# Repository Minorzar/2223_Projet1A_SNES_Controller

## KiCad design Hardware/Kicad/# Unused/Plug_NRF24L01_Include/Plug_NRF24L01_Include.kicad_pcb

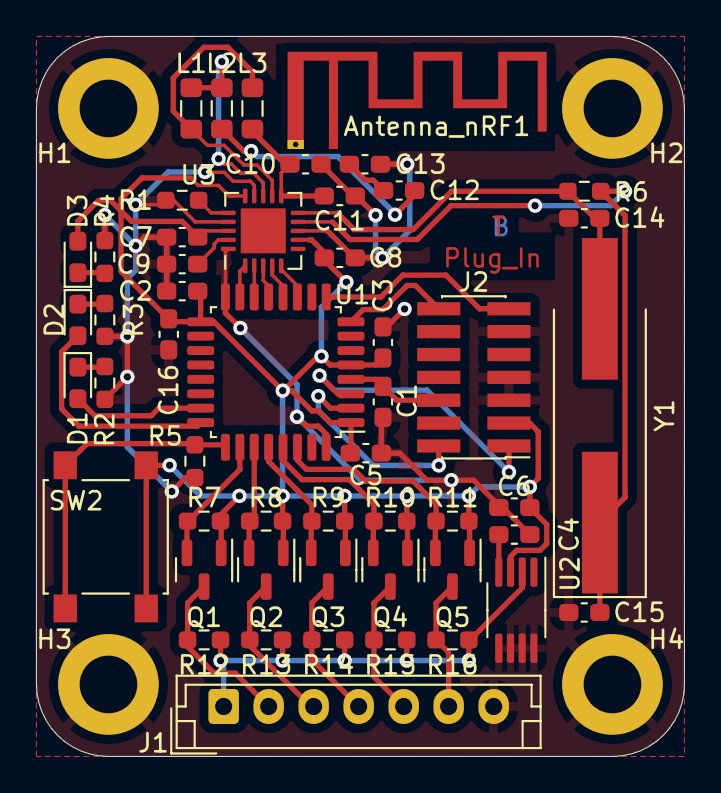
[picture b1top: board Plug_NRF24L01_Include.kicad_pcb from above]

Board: 2 copper layers, 36.0 x 40.0 mm, 55 parts (0 on the bottom side), 39 nets.

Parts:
Antenna_nRF1: Texas_SWRA117D_2.4GHz_Right
C1, C2, C3, C5: 100n; C_0603_1608Metric_Pad1.08x0.95mm_HandSolder
C4: 470p; C_0603_1608Metric_Pad1.08x0.95mm_HandSolder
C6: 2.2u; C_0603_1608Metric_Pad1.08x0.95mm_HandSolder
C7: 10n; C_0603_1608Metric_Pad1.08x0.95mm_HandSolder
C8: 1n; C_0603_1608Metric_Pad1.08x0.95mm_HandSolder
C9: 33n; C_0603_1608Metric_Pad1.08x0.95mm_HandSolder
C10: 2.2n; C_0603_1608Metric_Pad1.08x0.95mm_HandSolder
C11: 4.7p; C_0603_1608Metric_Pad1.08x0.95mm_HandSolder
C12: 1.5p; C_0603_1608Metric_Pad1.08x0.95mm_HandSolder
C13: 1.0p; C_0603_1608Metric_Pad1.08x0.95mm_HandSolder
C14, C15: 22p; C_0603_1608Metric_Pad1.08x0.95mm_HandSolder
C16: 10u; C_0603_1608Metric_Pad1.08x0.95mm_HandSolder
D1, D2: LED_Small; D_0603_1608Metric_Pad1.05x0.95mm_HandSolder
D3: LED; D_0603_1608Metric_Pad1.05x0.95mm_HandSolder
H1, H2, H3, H4: MountingHole_Pad; MountingHole_3.2mm_M3_DIN965_Pad
J1: Conn_01x07_Socket; JST_EH_B7B-EH-A_1x07_P2.50mm_Vertical
J2: Conn_02x07_Odd_Even; PinHeader_2x07_P1.27mm_Vertical_SMD
L1: 8.2n; L_0805_2012Metric_Pad1.05x1.20mm_HandSolder
L2: 3.9n; L_0805_2012Metric_Pad1.05x1.20mm_HandSolder
L3: 2.7n; L_0805_2012Metric_Pad1.05x1.20mm_HandSolder
Q1, Q2, Q3, Q4, Q5: 2N7002; SOT-23
R1: 22k; R_0603_1608Metric_Pad0.98x0.95mm_HandSolder
R2, R3, R4: 1k; R_0603_1608Metric_Pad0.98x0.95mm_HandSolder
R5, R7, R8, R9, R10, R11, R12, R13, R14, R15, R16: 10k; R_0603_1608Metric_Pad0.98x0.95mm_HandSolder
R6: 1M; R_0603_1608Metric_Pad0.98x0.95mm_HandSolder
SW2: SW_SPST; SW_SPST_B3S-1000
U1: STM32L412KBTx; LQFP-32_7x7mm_P0.8mm
U2: MIC5219-3.3YMM; MSOP-8_3x3mm_P0.65mm
U3: nRF24L01P; QFN-20-1EP_4x4mm_P0.5mm_EP2.5x2.5mm
Y1: 16MHz; Crystal_SMD_HC49-SD_HandSoldering

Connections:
+3.3V: C2.1, C3.1, C5.1, C6.1, C7.1, C8.1, C16.1, D3.2 (A), J2.3, Q1.1 (G), Q2.1 (G), Q3.1 (G), Q4.1 (G), Q5.1 (G), R7.1, R8.1, R9.1, R10.1, R11.1, SW2.2 (B), U1.1 (VDD), U1.5 (VDDA), U1.17 (VDD), U2.3 (OUT), U3.7 (VDD), U3.15 (VDD), U3.18 (VDD)
+5V: J1.1, R12.1, R13.1, R14.1, R15.1, R16.1, U2.2 (IN)
ANT1: L1.2, L3.1, U3.12 (ANT1)
ANT2: L1.1, L2.1, U3.13 (ANT2)
Appairing_Btn: R5.1, SW2.1 (A), U1.25 (PA15)
Chip_Enable: U1.15 (PB1), U3.1 (CE)
Data_Clock_SNES: J1.2, Q1.3 (D), R12.2
Data_Clock_STM32: Q1.2 (S), R7.2, U1.26 (PB3)
Data_Latch_SNES: J1.3, Q2.3 (D), R13.2
Data_Latch_STM32: Q2.2 (S), R8.2, U1.27 (PB4)
GND: C1.1, C2.2, C3.2, C4.2, C5.2, C6.2, C7.2, C8.2, C9.2, C10.2, C11.2, C13.1, C14.2, C15.2, C16.2, H1.1, H2.1, H3.1, H4.1, J1.7, J2.5, J2.7, J2.11, R1.2, R2.2, R3.2, R4.2, R5.2, U1.16 (VSS), U1.32 (VSS), U2.5 (GND), U2.6 (GND), U2.7 (GND), U2.8 (GND), U3.8 (VSS), U3.14 (VSS), U3.17 (VSS), U3.20 (VSS)
IOBit_SNES: J1.6, Q5.3 (D), R16.2
IOBit_STM32: Q5.2 (S), R11.2, U1.30 (PB7)
NRST: C1.2, J2.6, U1.4 (NRST)
unnamed: C12.2, L2.2
unnamed: D1.1 (K), R2.1
unnamed: D2.1 (K), R3.1
unnamed: D3.1 (K), R4.1
unnamed: C4.1, U2.4 (BP)
unnamed: C9.1, U3.19 (DVDD)
unnamed: R1.1, U3.16 (IREF)
Player1_LED: D1.2 (A), U1.23 (PA13)
RF_Output: Antenna_nRF1.1 (Feed_point), C12.1, C13.2
SPI_Chip_Select: U1.14 (PB0), U3.2 (CSN)
SPI_Clock: U1.13 (PA7), U3.3 (SCK)
SPI_Digital_Input: U1.12 (PA6), U3.4 (MOSI)
SPI_Digital_Output: U1.11 (PA5), U3.5 (MISO)
SWDCK: J2.14, U1.8 (PA2)
SWDIO: J2.13, U1.9 (PA3)
Serial_Data1_SNES: J1.4, Q3.3 (D), R14.2
Serial_Data1_STM32: Q3.2 (S), R9.2, U1.28 (PB5)
Serial_Data2_SNES: J1.5, Q4.3 (D), R15.2
Serial_Data2_STM32: Q4.2 (S), R10.2, U1.29 (PB6)
Status_LED: D2.2 (A), U1.24 (PA14)
USART2_RX: J2.1, U1.3 (PC15)
USART2_TX: J2.2, U1.2 (PC14)
VDD_PA: C10.1, C11.1, L3.2, U3.11 (VDD_PA)
XC1: C14.1, R6.1, U3.10 (XC1), Y1.2
XC2: C15.1, R6.2, U3.9 (XC2), Y1.1

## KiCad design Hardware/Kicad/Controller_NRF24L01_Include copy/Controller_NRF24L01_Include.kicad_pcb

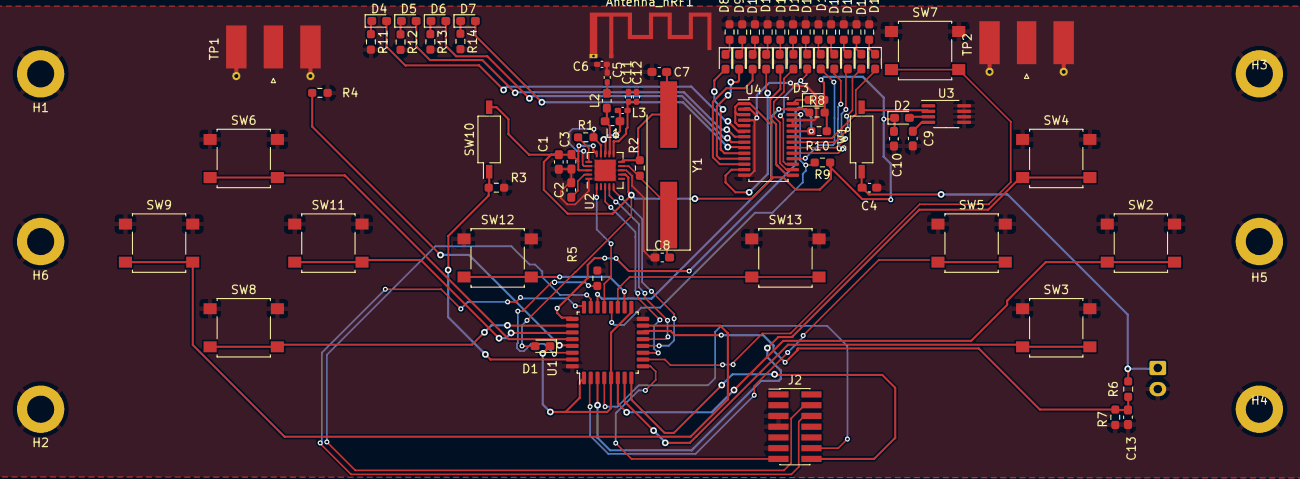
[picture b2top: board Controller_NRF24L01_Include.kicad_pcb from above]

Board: 2 copper layers, 90 parts (1 on the bottom side), 76 nets.

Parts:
Antenna_nRF1: Texas_SWRA117D_2.4GHz_Right
C1: 10nF; C_0603_1608Metric_Pad1.08x0.95mm_HandSolder
C2: 33nF; C_0603_1608Metric_Pad1.08x0.95mm_HandSolder
C3, C13: 1nF; C_0603_1608Metric_Pad1.08x0.95mm_HandSolder
C4: 1u; C_0603_1608Metric_Pad1.08x0.95mm_HandSolder
C5: 1.5pF; C_0402_1005Metric_Pad0.74x0.62mm_HandSolder
C6: 1.0pF; C_0402_1005Metric_Pad0.74x0.62mm_HandSolder
C7, C8: 22nF; C_0603_1608Metric_Pad1.08x0.95mm_HandSolder
C9: C_Small; C_0603_1608Metric_Pad1.08x0.95mm_HandSolder
C10: 100nF; C_0603_1608Metric_Pad1.08x0.95mm_HandSolder
C11: 2.2nF; C_0402_1005Metric_Pad0.74x0.62mm_HandSolder
C12: 4.7pF; C_0402_1005Metric_Pad0.74x0.62mm_HandSolder
D1: D_Small; D_0603_1608Metric_Pad1.05x0.95mm_HandSolder
D2: LED_Small; LED_0603_1608Metric_Pad1.05x0.95mm_HandSolder
D3: D_Small; LED_0603_1608Metric_Pad1.05x0.95mm_HandSolder
D4: G1; LED_0603_1608Metric_Pad1.05x0.95mm_HandSolder
D5: G2; LED_0603_1608Metric_Pad1.05x0.95mm_HandSolder
D6: G3; LED_0603_1608Metric_Pad1.05x0.95mm_HandSolder
D7: G4; LED_0603_1608Metric_Pad1.05x0.95mm_HandSolder
D8: G5; LED_0603_1608Metric_Pad1.05x0.95mm_HandSolder
D9: G6; LED_0603_1608Metric_Pad1.05x0.95mm_HandSolder
D10: G7; LED_0603_1608Metric_Pad1.05x0.95mm_HandSolder
D11: G8; LED_0603_1608Metric_Pad1.05x0.95mm_HandSolder
D12: O1; LED_0603_1608Metric_Pad1.05x0.95mm_HandSolder
D13: O2; LED_0603_1608Metric_Pad1.05x0.95mm_HandSolder
D14: O3; LED_0603_1608Metric_Pad1.05x0.95mm_HandSolder
D15: O4; LED_0603_1608Metric_Pad1.05x0.95mm_HandSolder
D16: R1; LED_0603_1608Metric_Pad1.05x0.95mm_HandSolder
D17: R2; LED_0603_1608Metric_Pad1.05x0.95mm_HandSolder
D18: R3; LED_0603_1608Metric_Pad1.05x0.95mm_HandSolder
D19: R4; LED_0603_1608Metric_Pad1.05x0.95mm_HandSolder
H1, H2, H3, H4, H5, H6: MountingHole_Pad; MountingHole_3.2mm_M3_DIN965_Pad
J1: Conn_01x02; JST_XH_B2B-XH-A_1x02_P2.50mm_Vertical
J2: Conn_02x07_Odd_Even; PinHeader_2x07_P1.27mm_Vertical_SMD
L1: 8.2nH; L_0603_1608Metric_Pad1.05x0.95mm_HandSolder
L2: 3.9nH; L_0603_1608Metric_Pad1.05x0.95mm_HandSolder
L3: 2.7nH; L_0402_1005Metric_Pad0.77x0.64mm_HandSolder
R1: 22K; R_0603_1608Metric_Pad0.98x0.95mm_HandSolder
R2, R6, R7: 1M; R_0603_1608Metric_Pad0.98x0.95mm_HandSolder
R3, R4, R5, R11, R12, R13, R14, R15, R16, R17, R18, R19, R20, R21, R22, R23, R24, R25, R26: 1K; R_0603_1608Metric_Pad0.98x0.95mm_HandSolder
R8, R9, R10: 10K; R_0603_1608Metric_Pad0.98x0.95mm_HandSolder
SW1, SW10: SW_DIP_x01; SW_DIP_SPSTx01_Slide_Copal_CHS-01B_W7.62mm_P1.27mm
SW2, SW3, SW4, SW5, SW6, SW7, SW8, SW9, SW11, SW12, SW13: SW_SPST; SW_SPST_B3S-1000
TP1: R; SMA_Molex_73251-1153_EdgeMount_Horizontal
TP2: L; SMA_Molex_73251-1153_EdgeMount_Horizontal
U1: STM32L412KBTx; LQFP-32_7x7mm_P0.8mm
U2: NRF24L01; QFN-20-1EP_4x4mm_P0.5mm_EP2.5x2.5mm
U3: MIC5219-3.3YMM; MSOP-8_3x3mm_P0.65mm
U4: PCA9685PW; TSSOP-28_4.4x9.7mm_P0.65mm
Y1: 16MHz; Crystal_SMD_HC49-SD_HandSoldering

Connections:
A_Button: SW2.2 (B), U1.6 (PA0)
Antenna: Antenna_nRF1.1 (Feed_point), C5.1, C6.1
B_Button: SW3.2 (B), U1.7 (PA1)
DC_Button: SW11.2 (B), U1.27 (PB4)
DIODE_CLK: R9.2, U1.20 (PA10), U4.26 (SCL)
DIODE_OE: R10.1, U1.25 (PA15), U4.23 (~OE)
DIODE_SDA: R8.1, U1.22 (PA12), U4.27 (SDA)
Digital_Out_Put: U1.12 (PA6), U2.5 (MISO)
GND: Antenna_nRF1.2 (GND), C1.2, C2.2, C3.2, C4.2, C6.2, C7.1, C8.1, C9.2, C10.2, C11.2, C12.1, C13.2, H1.1, H2.1, H3.1, H4.1, H5.1, H6.1, J1.2, J2.5, J2.7, J2.11, R1.2, R3.2, R4.2, R5.2, R7.2, R11.2, R12.2, R13.2, R14.2, R15.2, R16.2, R17.2, R18.2, R19.2, R20.2, R21.2, R22.2, R23.2, R24.2, R25.2, R26.2, SW2.1 (A), SW3.1 (A), SW4.1 (A), SW5.1 (A), SW6.1 (A), SW7.1 (A), SW8.1 (A), SW9.1 (A), SW11.1 (A), SW12.1 (A), SW13.1 (A), U1.16 (VSS), U1.32 (VSS), U2.8 (VSS), U2.14 (VSS), U2.17 (VSS), U2.20 (VSS), U3.5 (GND), U3.6 (GND), U3.7 (GND), U3.8 (GND), U4.2 (A1), U4.4 (A3), U4.14 (VSS), U4.24 (A5), U4.25 (EXTCLK)
Glob_Alim: C1.1, C3.1, C10.1, D1.2 (A), D2.1 (K), D3.2 (A), R8.2, R9.1, R10.2, SW10.2, U2.7 (VDD), U2.15 (VDD), U2.18 (VDD), U4.1 (A0), U4.3 (A2), U4.5 (A4)
L: R5.1, U1.30 (PB7)
LC_Button: SW8.2 (B), U1.26 (PB3)
Li-ion: C4.1, J1.1, R6.1, SW1.1
MOSI: U1.13 (PA7), U2.4 (MOSI)
NES/SNES_switcher: R3.1, SW10.1, U1.31 (PH3)
unnamed: D1.1 (K), U1.1 (VDD), U1.5 (VDDA), U1.17 (VDD)
unnamed: SW1.2, U3.2 (IN)
unnamed: D3.1 (K), U4.28 (VDD)
unnamed: C5.2, L2.2
unnamed: D2.2 (A), U3.3 (OUT)
unnamed: D4.2 (A), U4.6 (LED0)
unnamed: D4.1 (K), R11.1
unnamed: D5.2 (A), U4.7 (LED1)
unnamed: D5.1 (K), R12.1
unnamed: D6.2 (A), U4.8 (LED2)
unnamed: D6.1 (K), R13.1
unnamed: D7.2 (A), U4.9 (LED3)
unnamed: D7.1 (K), R14.1
unnamed: D8.2 (A), U4.10 (LED4)
unnamed: D8.1 (K), R15.1
unnamed: D9.2 (A), U4.11 (LED5)
unnamed: D9.1 (K), R16.1
unnamed: D10.2 (A), U4.12 (LED6)
unnamed: D10.1 (K), R17.1
unnamed: D11.2 (A), U4.13 (LED7)
unnamed: D11.1 (K), R18.1
unnamed: D12.2 (A), U4.15 (LED8)
unnamed: D12.1 (K), R19.1
unnamed: D13.2 (A), U4.16 (LED9)
unnamed: D13.1 (K), R20.1
unnamed: D14.2 (A), U4.17 (LED10)
unnamed: D14.1 (K), R21.1
unnamed: D15.2 (A), U4.18 (LED11)
unnamed: D15.1 (K), R22.1
unnamed: D16.2 (A), U4.19 (LED12)
unnamed: D16.1 (K), R23.1
unnamed: D17.2 (A), U4.20 (LED13)
unnamed: D17.1 (K), R24.1
unnamed: D18.2 (A), U4.21 (LED14)
unnamed: D18.1 (K), R25.1
unnamed: D19.2 (A), U4.22 (LED15)
unnamed: D19.1 (K), R26.1
unnamed: L1.2, L2.1, U2.12 (ANT1)
unnamed: L1.1, L3.1, U2.13 (ANT2)
unnamed: C2.1, U2.19 (DVDD)
unnamed: R1.1, U2.16 (IREF)
unnamed: C7.2, R2.1, U2.10 (XC1), Y1.2
unnamed: C8.2, R2.2, U2.9 (XC2), Y1.1
unnamed: C9.1, U3.4 (BP)
Order_Search: SW7.2 (B), U1.10 (PA4)
POWER_CHECK: C13.1, R6.2, R7.1, U1.14 (PB0)
Pin_Clock: U1.11 (PA5), U2.3 (SCK)
R: R4.1, U1.29 (PB6)
RC_Button: SW9.2 (B), U1.15 (PB1)
RX/TX: U1.21 (PA11), U2.1 (CE)
Reset_Buton: J2.12, U1.4 (NRST)
Return_ANT: C11.1, C12.2, L3.2, U2.11 (VDD_PA)
SE_Button: SW13.2 (B), U1.19 (PA9)
ST_Button: SW12.2 (B), U1.18 (PA8)
SWDCK: J2.6, U1.24 (PA14)
SWDIO: J2.4, U1.23 (PA13)
UC_Button: SW6.2 (B), U1.28 (PB5)
USART2_RX: J2.13, U1.9 (PA3)
USART2_TX: J2.14, U1.8 (PA2)
X_Button: SW4.2 (B), U1.3 (PC15)
Y_Button: SW5.2 (B), U1.2 (PC14)

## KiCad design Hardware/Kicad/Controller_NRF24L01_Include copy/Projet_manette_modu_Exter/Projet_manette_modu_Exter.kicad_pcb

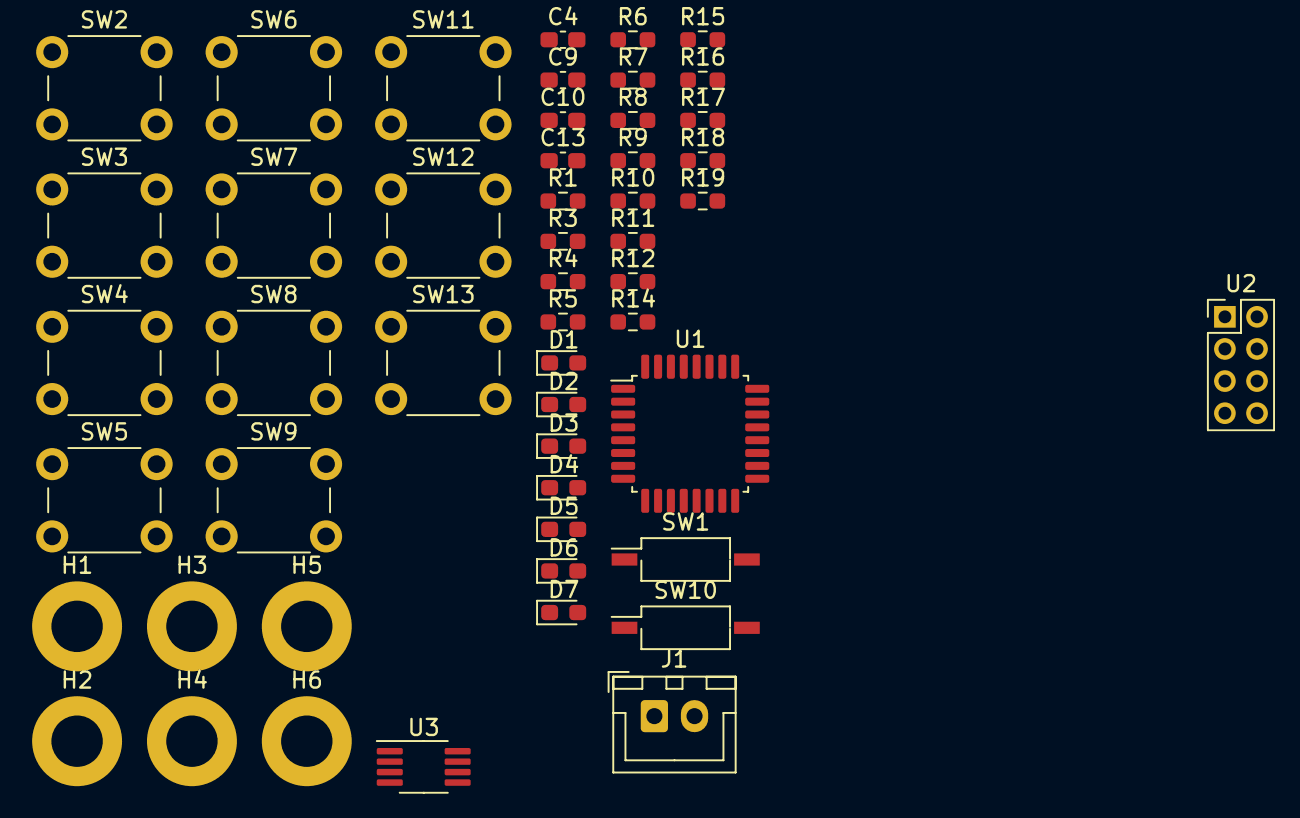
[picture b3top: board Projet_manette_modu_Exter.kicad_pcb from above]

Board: 2 copper layers, 51 parts (0 on the bottom side), 29 nets, no tracks yet.

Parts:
C4: 1u; C_0603_1608Metric_Pad1.08x0.95mm_HandSolder
C9: C_Small; C_0603_1608Metric_Pad1.08x0.95mm_HandSolder
C10: 100nF; C_0603_1608Metric_Pad1.08x0.95mm_HandSolder
C13: 1nF; C_0603_1608Metric_Pad1.08x0.95mm_HandSolder
D1: D_Small; D_0603_1608Metric_Pad1.05x0.95mm_HandSolder
D2: LED_Small; LED_0603_1608Metric_Pad1.05x0.95mm_HandSolder
D3, D4, D5, D6, D7: LED; LED_0603_1608Metric_Pad1.05x0.95mm_HandSolder
H1, H2, H3, H4, H5, H6: MountingHole_Pad; MountingHole_3.2mm_M3_DIN965_Pad
J1: Conn_01x02; JST_XH_B2B-XH-A_1x02_P2.50mm_Vertical
R1, R3, R4, R5, R6, R7, R8, R9, R10, R12, R15, R17, R19: 1K; R_0603_1608Metric_Pad0.98x0.95mm_HandSolder
R11, R14, R16, R18: R_Small; R_0603_1608Metric_Pad0.98x0.95mm_HandSolder
SW1, SW10: SW_DIP_x01; SW_DIP_SPSTx01_Slide_Copal_CHS-01B_W7.62mm_P1.27mm
SW2, SW3, SW4, SW5, SW6, SW7, SW8, SW9, SW11, SW12, SW13: SW_Push; SW_PUSH_6mm_H5mm
U1: STM32L412KBTx; LQFP-32_7x7mm_P0.8mm
U2: nRF24_Full; PinHeader_2x04_P2.00mm_Vertical
U3: MIC5219-3.3YMM; MSOP-8_3x3mm_P0.65mm

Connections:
A_Button: R3.1, SW2.1, U1.6 (PA0)
B_Button: R4.1, SW3.1, U1.7 (PA1)
DC_Button: R15.1, SW11.1, U1.11 (PA5)
Digital_Out_Put: U1.27 (PB4), U2.7 (MISO)
GND: C4.2, C9.2, C10.2, C13.2, D4.1 (K), D5.1 (K), D6.1 (K), D7.1 (K), H1.1, H2.1, H3.1, H4.1, H5.1, H6.1, J1.2, R1.2, R3.2, R4.2, R5.2, R6.2, R7.2, R8.2, R9.2, R10.2, R12.2, R15.2, R17.2, R19.2, U1.16 (VSS), U1.32 (VSS), U2.1 (GND), U3.5 (GND), U3.6 (GND), U3.7 (GND), U3.8 (GND)
Glob_Alim: C10.1, D1.2 (A), D2.1 (K), SW2.2, SW3.2, SW4.2, SW5.2, SW6.2, SW7.2, SW8.2, SW9.2, SW10.2, SW11.2, SW12.2, SW13.2, U2.2 (VCC)
LC_Button: R8.1, SW8.1, U1.12 (PA6)
LED_Order: D3.2 (A), U1.22 (PA12)
Li-ion: C4.1, C13.1, J1.1, R11.1, R14.1, R16.1, R18.1, SW1.1
MOSI: U1.28 (PB5), U2.6 (MOSI)
NES/SNES_switcher: R1.1, SW10.1, U1.23 (PA13)
unnamed: D1.1 (K), U1.1 (VDD), U1.5 (VDDA), U1.17 (VDD)
unnamed: D2.2 (A), U3.3 (OUT)
unnamed: D3.1 (K), R10.1
unnamed: D4.2 (A), R11.2
unnamed: D5.2 (A), R14.2
unnamed: D6.2 (A), R16.2
unnamed: D7.2 (A), R18.2
unnamed: C9.1, U3.4 (BP)
unnamed: SW1.2, U3.2 (IN)
Order_Search: R9.1, SW7.1, U1.20 (PA10)
Pin_Clock: U1.26 (PB3), U2.5 (SCK)
RC_Button: R12.1, SW9.1, U1.13 (PA7)
RX/TX: U1.21 (PA11), U2.3 (CE)
SE_Button: R19.1, SW13.1, U1.19 (PA9)
ST_Button: R17.1, SW12.1, U1.18 (PA8)
UC_Button: R7.1, SW6.1, U1.10 (PA4)
X_Button: R5.1, SW4.1, U1.8 (PA2)
Y_Button: R6.1, SW5.1, U1.9 (PA3)

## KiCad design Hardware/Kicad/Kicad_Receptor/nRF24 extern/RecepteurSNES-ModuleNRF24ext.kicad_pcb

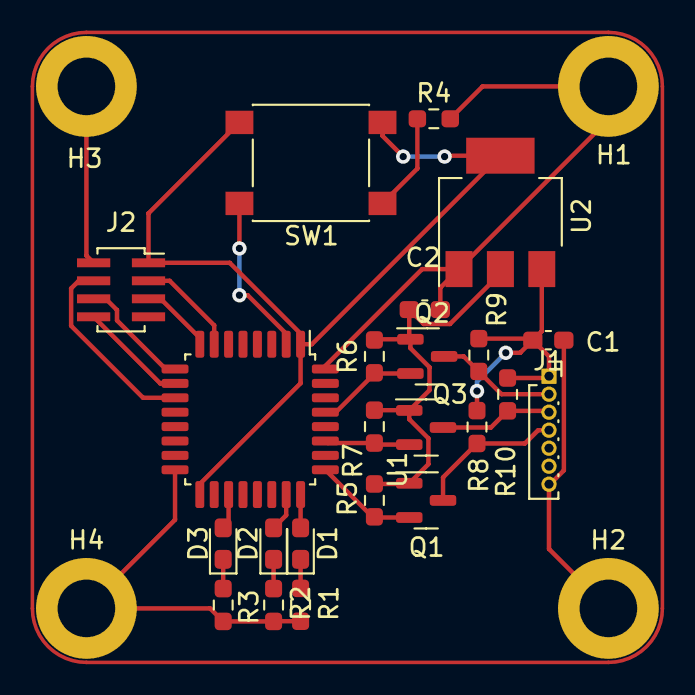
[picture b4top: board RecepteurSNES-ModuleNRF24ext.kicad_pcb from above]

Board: 2 copper layers, 27 parts (0 on the bottom side), 21 nets.

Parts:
C1, C2: 1u; C_0603_1608Metric_Pad1.08x0.95mm_HandSolder
D1, D2, D3: LED_Small; D_0603_1608Metric_Pad1.05x0.95mm_HandSolder
H1, H2, H3, H4: MountingHole_Pad; MountingHole_3.2mm_M3_DIN965_Pad
J1: Conn_01x07_Socket; PinSocket_1x07_P1.00mm_Vertical
J2: Conn_01x08_Socket; PinSocket_2x04_P1.00mm_Vertical_SMD
Q1, Q2, Q3: 2N7002; SOT-23
R1, R2, R3: 1k; R_0603_1608Metric_Pad0.98x0.95mm_HandSolder
R4, R5, R6, R7, R8, R9, R10: 10k; R_0603_1608Metric_Pad0.98x0.95mm_HandSolder
SW1: SW_Push; SW_Push_1P1T_NO_6x6mm_H9.5mm
U1: STM32L412KBTx; LQFP-32_7x7mm_P0.8mm
U2: AMS1117-3.3; SOT-223-3_TabPin2

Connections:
+3.3V: C2.1, J2.1, Q1.1 (G), Q2.1 (G), Q3.1 (G), R5.1, R6.1, R7.1, SW1.1, U1.1 (VDD), U1.17 (VDD), U2.2 (VO)
+5V: C1.1, J1.1, R8.1, R9.1, R10.1, U2.3 (VI)
Appairing_Btn: R4.1, SW1.2, U1.2 (PC14)
Chip_Enable: J2.4, U1.11 (PA5)
Data_Clock_SNES: J1.2, Q2.3 (D), R9.2
Data_Clock_STM32: Q2.2 (S), R6.2, U1.29 (PB6)
Data_Latch_SNES: J1.3, Q3.3 (D), R10.2
Data_Latch_STM32: Q3.2 (S), R7.2, U1.27 (PB4)
GND: C1.2, C2.2, H1.1, H2.1, H3.1, H4.1, J1.7, J2.2, R1.2, R2.2, R3.2, R4.2, U1.16 (VSS), U1.32 (VSS), U2.1 (GND)
unnamed: D1.1 (K), R1.1
unnamed: D2.1 (K), R2.1
unnamed: D3.1 (K), R3.1
Player1_LED: D1.2 (A), U1.24 (PA14)
Player2_LED: D2.2 (A), U1.23 (PA13)
SPI_Chip_Select: J2.3, U1.7 (PA1)
SPI_Clock: J2.6, U1.9 (PA3)
SPI_Digital_Input: J2.5, U1.8 (PA2)
SPI_Digital_Output: J2.8, U1.10 (PA4)
Serial_Data_SNES: J1.4, Q1.3 (D), R8.2
Serial_Data_STM32: Q1.2 (S), R5.2, U1.25 (PA15)
Status_LED: D3.2 (A), U1.19 (PA9)

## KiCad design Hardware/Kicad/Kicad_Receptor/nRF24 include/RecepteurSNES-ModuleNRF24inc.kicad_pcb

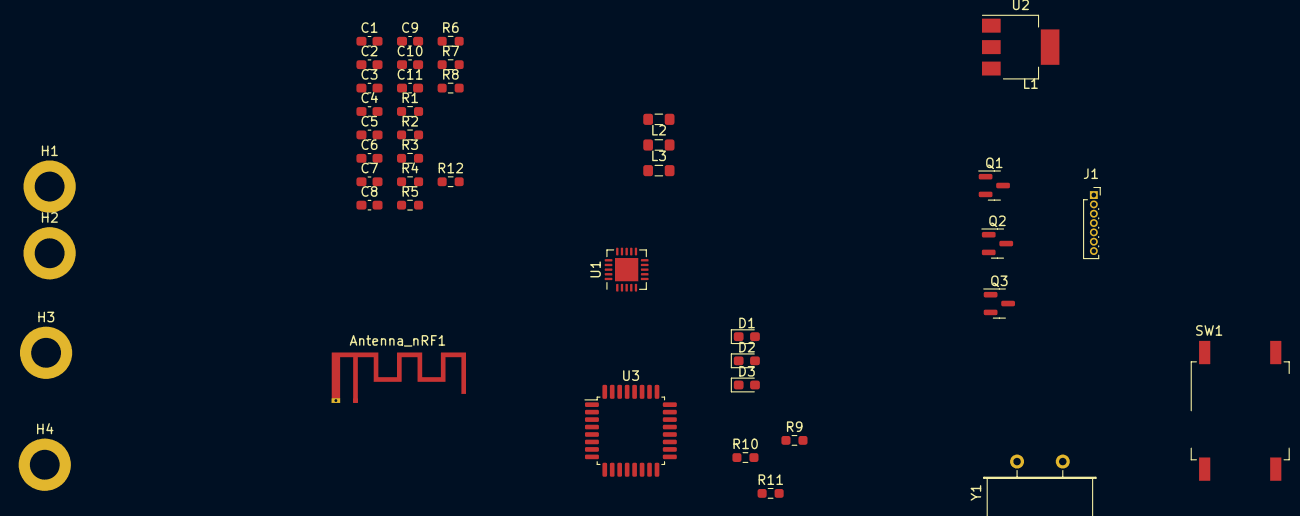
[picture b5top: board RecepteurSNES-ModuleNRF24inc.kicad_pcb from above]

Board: 2 copper layers, 43 parts (0 on the bottom side), 30 nets, no tracks yet.

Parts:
Antenna_nRF1: Texas_SWRA117D_2.4GHz_Right
C1, C2: 1u; C_0603_1608Metric_Pad1.08x0.95mm_HandSolder
C3: 33n; C_0603_1608Metric_Pad1.08x0.95mm_HandSolder
C4: 10n; C_0603_1608Metric_Pad1.08x0.95mm_HandSolder
C5: 1n; C_0603_1608Metric_Pad1.08x0.95mm_HandSolder
C6: 2.2n; C_0603_1608Metric_Pad1.08x0.95mm_HandSolder
C7: 4.7p; C_0603_1608Metric_Pad1.08x0.95mm_HandSolder
C8: 1.5p; C_0603_1608Metric_Pad1.08x0.95mm_HandSolder
C9: 1.0p; C_0603_1608Metric_Pad1.08x0.95mm_HandSolder
C10, C11: 22p; C_0603_1608Metric_Pad1.08x0.95mm_HandSolder
D1, D2, D3: LED_Small; D_0603_1608Metric_Pad1.05x0.95mm_HandSolder
H1, H2, H3, H4: MountingHole_Pad; MountingHole_3.2mm_M3_DIN965_Pad
J1: Conn_01x07_Socket; PinSocket_1x07_P1.00mm_Vertical
L1: 8.2n; L_0805_2012Metric_Pad1.05x1.20mm_HandSolder
L2: 3.9n; L_0805_2012Metric_Pad1.05x1.20mm_HandSolder
L3: 2.7n; L_0805_2012Metric_Pad1.05x1.20mm_HandSolder
Q1, Q2, Q3: 2N7002; SOT-23
R1: 22k; R_0603_1608Metric_Pad0.98x0.95mm_HandSolder
R2: 1M; R_0603_1608Metric_Pad0.98x0.95mm_HandSolder
R3, R4, R5, R6, R7, R8, R12: 10k; R_0603_1608Metric_Pad0.98x0.95mm_HandSolder
R9, R10, R11: 1k; R_0603_1608Metric_Pad0.98x0.95mm_HandSolder
SW1: SW_Push; SW_MEC_5GSH9
U1: NRF24L01; QFN-20-1EP_4x4mm_P0.5mm_EP2.5x2.5mm
U2: AMS1117-3.3; SOT-223-3_TabPin2
U3: STM32L412KBTx; LQFP-32_7x7mm_P0.8mm
Y1: 16 MHz; Crystal_HC49-U_Horizontal

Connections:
+5V: C1.1, J1.1, R3.1, R6.1, R8.1, U2.3 (VI)
ANT1: L1.2, L3.1, U1.12 (ANT1)
ANT2: L1.1, L2.1, U1.13 (ANT2)
Appairing_Btn: R12.1, SW1.2, U3.25 (PA15)
Chip_Enable: U1.1 (CE), U3.30 (PB7)
Data_Clock_SNES: J1.2, Q2.3 (D), R6.2
Data_Clock_STM32: Q2.2 (S), R5.2, U3.8 (PA2)
Data_Latch_SNES: J1.3, Q3.3 (D), R8.2
Data_Latch_STM32: Q3.2 (S), R7.2, U3.9 (PA3)
GND: Antenna_nRF1.2 (GND), C1.2, C2.2, C3.2, C4.2, C5.2, C6.2, C7.2, C9.1, C10.2, C11.2, H1.1, H2.1, H3.1, H4.1, J1.7, R1.2, R9.2, R10.2, R11.2, R12.2, U1.8 (VSS), U1.14 (VSS), U1.17 (VSS), U1.20 (VSS), U2.1 (GND), U3.16 (VSS), U3.32 (VSS)
unnamed: C8.2, L2.2
unnamed: D1.1 (K), R9.1
unnamed: D2.1 (K), R10.1
unnamed: D3.1 (K), R11.1
unnamed: C3.1, U1.19 (DVDD)
unnamed: R1.1, U1.16 (IREF)
Player1_LED: D2.2 (A), U3.23 (PA13)
Player2_LED: D1.2 (A), U3.24 (PA14)
RF_Output: Antenna_nRF1.1 (Feed_point), C8.1, C9.2
SPI_Chip_Select: U1.2 (CSN), U3.29 (PB6)
SPI_Clock: U1.3 (SCK), U3.26 (PB3)
SPI_Digital_Input: U1.4 (MOSI), U3.28 (PB5)
SPI_Digital_Output: U1.5 (MISO), U3.27 (PB4)
Serial_Data_SNES: J1.4, Q1.3 (D), R3.2
Serial_Data_STM32: Q1.2 (S), R4.2, U3.7 (PA1)
Status_LED: D3.2 (A), U3.22 (PA12)
VDD_NRF: C2.1, C4.1, C5.1, Q1.1 (G), Q2.1 (G), Q3.1 (G), R4.1, R5.1, R7.1, SW1.1, U1.7 (VDD), U1.15 (VDD), U1.18 (VDD), U2.2 (VO), U3.1 (VDD), U3.17 (VDD)
VDD_PA: C6.1, C7.1, L3.2, U1.11 (VDD_PA)
XC1: C10.1, R2.1, U1.10 (XC1), Y1.2
XC2: C11.1, R2.2, U1.9 (XC2), Y1.1
